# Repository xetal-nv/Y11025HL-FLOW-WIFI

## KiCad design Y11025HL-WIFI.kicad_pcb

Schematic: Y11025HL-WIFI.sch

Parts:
C1, C2, C4, C7, C10, C13, C15, C16: 10uF; C_0603_1608Metric
C3, C6, C8: 0.1uF; C_0603_1608Metric
C5: 10pF; C_0603_1608Metric
C9, C11: 470uF; CP_Elec_6.3x7.7
C12, C14, C17: 100nF; C_0603_1608Metric
C18, C20: 1uF; C_0603_1608Metric
C19: 470pF; C_0603_1608Metric
D1: LED1; LED_0603_1608Metric
D2: LED0; LED_0603_1608Metric
D3: LED; LED_0603_1608Metric
H1, H2, H3, H4: MountingHole_Pad; MountingHole_2.2mm_M2_Pad
J1: Barrel_Jack_Switch_Pin3Ring; BarrelJack_CLIFF_FC681465S_SMT_Horizontal
J2: Conn_01x05_Female; PinHeader_1x05_P2.54mm_Vertical
L1, L2: 10uH; L_0603_1608Metric
ML1: MLX90621
P1: JTAG; PinHeader_1x05_P1.27mm_Vertical
R1: 10K; R_0603_1608Metric
R2: 100K; R_0603_1608Metric
R3: 2.2k; R_0603_1608Metric
R4: 100k; R_0603_1608Metric
R5, R16, R19, R20: 4.7K; R_0603_1608Metric
R6: 590K; R_0603_1608Metric
R7: 174K; R_0603_1608Metric
R8, R9, R12: 4.7K DNP; R_0603_1608Metric
R10, R11, R18: 330; R_0603_1608Metric
R13, R14: 0; R_0603_1608Metric
R15: 10; R_0603_1608Metric
R17, R21: DNP; R_0603_1608Metric
SW1: WIFI RST; SW_SPST_B3U-1000P
U1: ESP-12E
U2: TLV767_DGN_ADJ; VSSOP-8_3.0x3.0mm_P0.65mm
U3: TLV767_DRV_ADJ; WSON-6-1EP_2x2mm_P0.65mm_EP1x1.6mm_ThermalVias
U4: LM1117-3.3; SOT-223-3_TabPin2
U5: dspic33ep256gp502-QFN; QFN-28-1EP_6x6mm_P0.65mm_EP4.25x4.25mm
U6: MIC5219-2.6; SOT-23-5

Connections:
2.6V: C20.2, L2.2, R21.2, U6.5 (OUT)
+3.3VA: C16.1, C17.1, C18.2, L1.2, P1.2, R15.1, R16.2, R19.1, R20.1, R21.1, U5.10 (Vdd), U6.1 (IN), U6.3 (EN)
+3V3: C8.1, C10.1, C11.1, J2.1, R1.1, R2.1, R8.2, R10.1, R11.1, SW1.2, U1.8 (VCC), U1.17 (GPIO2), U4.2 (VO)
+5V: C1.1, C3.1, J1.1, R4.1, U2.8 (IN), U3.6 (IN), U4.3 (VI)
CLK: P1.5, U5.3 (PGEC1/AN4/C1IN1+/RPI34/RB2)
CS: U1.20 (GPIO5), U5.18 (TDO/RP42/RB10)
DAT: P1.4, U5.4 (PGED1/AN5/C1IN1-/RP35/RB3)
DATA1: R12.2, R17.2, U1.4 (GPIO16), U5.15 (TMS/ASDA1/SDI1/RP41/RB9)
DATA2: R9.2, R14.2, U1.5 (GPIO14), U5.14 (TCK/CVREF1O/ASCL1/SDO1/RP40/T4CK/RB8)
EN: C4.1, R4.2, U1.19 (GPIO4), U2.5 (EN), U3.4 (EN)
FLASHPIN: D1.1 (K), J2.2, U1.18 (GPIO0)
GND: C1.2, C2.1, C3.2, C4.2, C6.2, C7.2, C8.2, C9.2, C10.2, C11.2, C12.2, C13.1, C14.2, C15.2, C16.2, C17.2, C18.1, C19.2, C20.1, D3.1 (K), H1.1, H2.1, H3.1, H4.1, J1.2, J1.3, J2.5, ML1.4 (VSS), P1.3, R3.1, R5.1, R7.1, R9.1, R12.1, U1.15 (GND), U2.4 (GND), U2.6 (GND), U3.3 (GND), U3.5 (GND), U4.1 (GND), U5.5 (Vss), U5.16 (Vss), U5.24 (AVss), U5.29 (PAD), U6.2 (GND)
LED0: D2.1 (K), R5.2, U1.16 (GPIO15)
MCLR: P1.1, R16.1, U5.26 (~MCLR~)
unnamed: C2.2, R2.2, U1.3 (CH_PD)
unnamed: C5.1, C6.1, C7.1, C9.1, L1.1, R6.2, U2.1 (OUT), U3.1 (OUT)
unnamed: C5.2, R6.1, R7.2, U2.2 (FB), U3.2 (FB)
unnamed: C12.1, R15.2, U5.25 (AVdd)
unnamed: C13.2, U5.17 (Vcap)
unnamed: C14.1, C15.1, L2.1, ML1.3 (VDD)
unnamed: C19.1, U6.4 (BP)
unnamed: D1.2 (A), R10.2
unnamed: D2.2 (A), R11.2
unnamed: D3.2 (A), R18.1
unnamed: R1.2, U1.1 (REST)
unnamed: R17.1, U5.28 (AN1/C2IN1+/RA1)
unnamed: R18.2, U5.27 (AN0/OA2OUT/RA0)
RESET: R3.2, SW1.1, U1.6 (GPIO12)
RX: J2.4, R13.1, U1.22 (TXD)
SCK: R8.1, R13.2, U1.7 (GPIO13), U5.13 (SCK1/RP39/INT0/RB7)
SCL1: ML1.1 (SCL), R20.2, U5.12 (PGEC2/ASCL2/RP38/RB6)
SDA1: ML1.2 (SDA), R19.2, U5.11 (PGED2/ASDA2/RP37/RB5)
TX: J2.3, R14.1, U1.21 (RXD)

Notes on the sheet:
3.5V generated

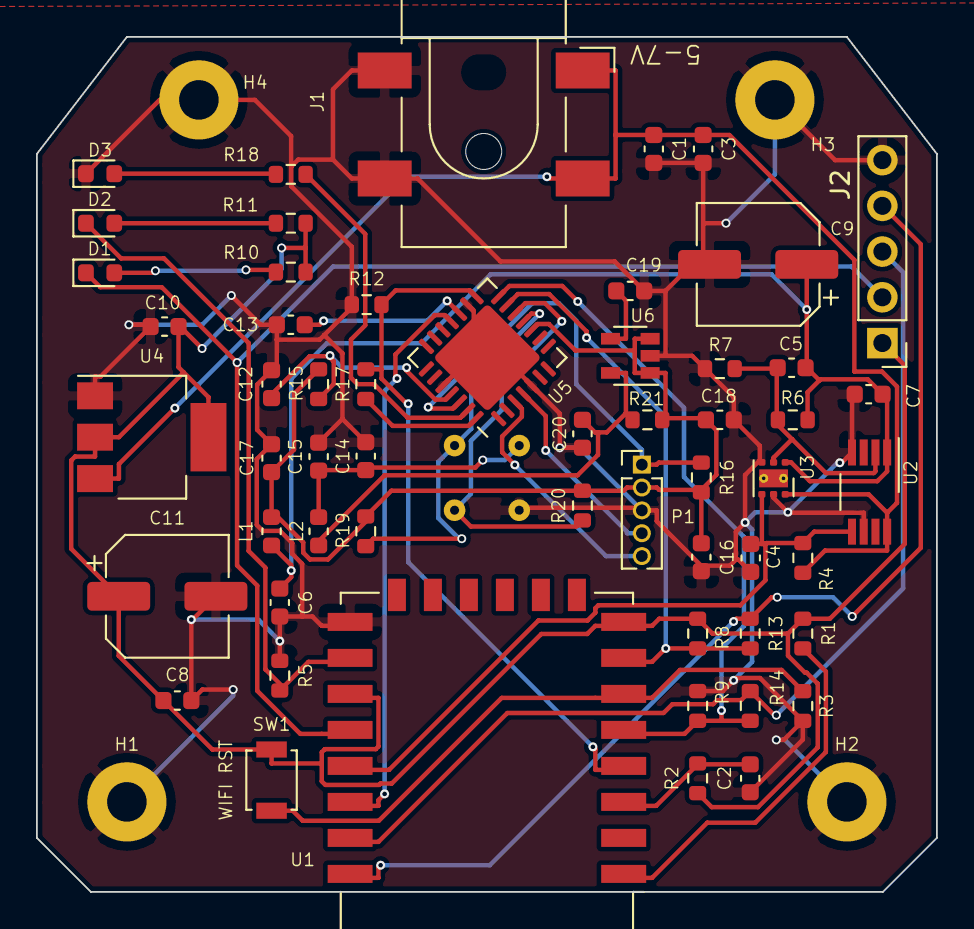
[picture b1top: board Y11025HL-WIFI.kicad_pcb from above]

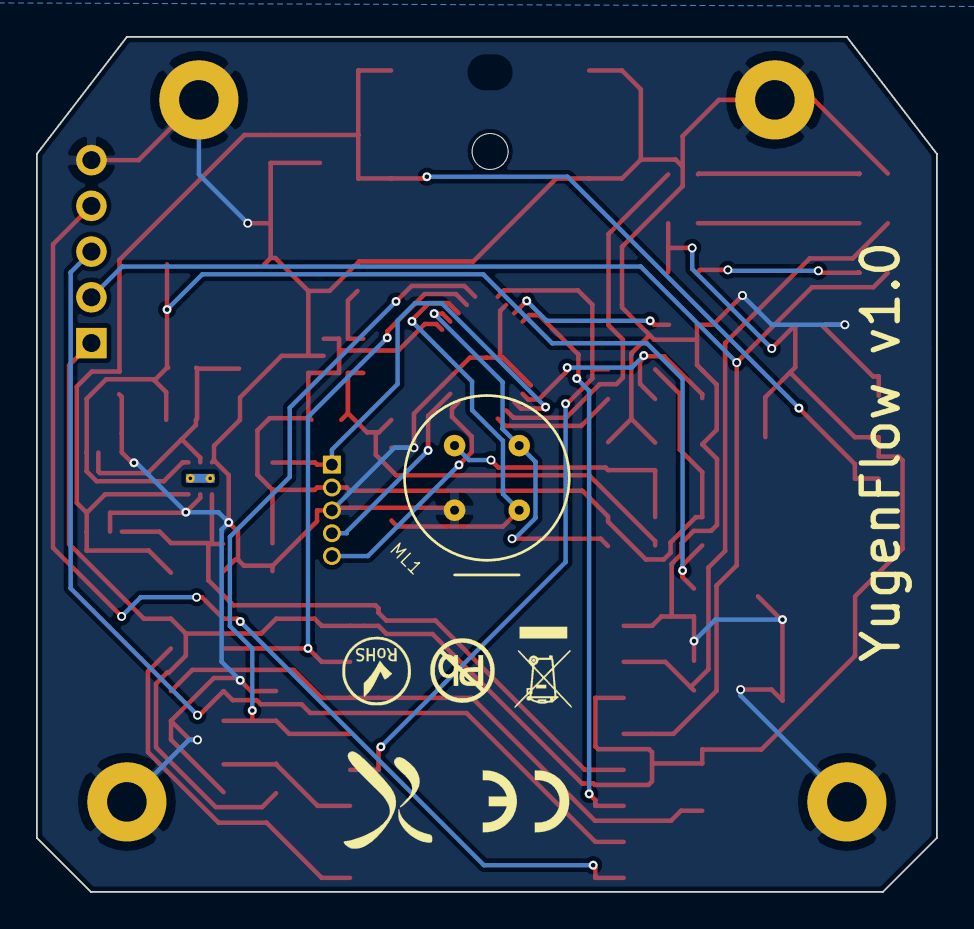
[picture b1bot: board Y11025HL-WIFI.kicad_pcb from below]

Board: 2 copper layers, 50.0 x 47.5 mm, 66 parts (6 on the bottom side), 33 nets.

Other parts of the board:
G1: LOGO; RoHS-Logo_3.8mm_SilkScreen
G2: LOGO; CE-Logo_6.8x4.8mm_SilkScreen
G3: LOGO; PB-Logo_3.7mm_SilkScreen
G4: LOGO; WEEE-Logo_3.2x4.5mm_SilkScreen
G5: LOGO; Xetal-Logo_6.7mm_SilkScreen

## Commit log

2021-03-19 tp turned 90d
2021-04-06 cleaned
